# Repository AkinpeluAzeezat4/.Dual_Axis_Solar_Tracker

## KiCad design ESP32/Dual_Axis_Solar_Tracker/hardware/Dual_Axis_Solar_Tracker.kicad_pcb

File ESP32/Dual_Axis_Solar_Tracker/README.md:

# Dual Axis Solar Tracker

## Overview

This project is a Dual Axis Solar Tracking System built using the ESP32-WROOM-32UE microcontroller and an L298D motor driver module. The system automatically tracks the direction of sunlight using four LDR sensors and positions the solar panel for maximum light exposure using two DC motors.

The tracker also includes:

- Automatic night detection and sleep mode
- Rotary encoder based calibration and control
- Direction indication LEDs
- Manual movement mode
- Saved calibration settings using ESP32 Preferences (NVS)

The project is designed using a modular architecture for easier maintenance, debugging, scalability, and future upgrades.

---

# Features

- Dual axis solar tracking
- Automatic horizontal and vertical alignment
- Night detection using dedicated LDR
- Deep sleep power saving mode
- Rotary encoder controlled calibration
- Manual motor control mode
- Direction indication LEDs
- Saved calibration settings
- PWM motor speed control
- Modular PlatformIO structure

---

# Hardware Used

## Main Controller

- ESP32-WROOM-32UE

## Motor Driver

- L298D Dual H-Bridge Motor Driver

## Sensors

- 4 × LDRs for sun tracking
- 1 × LDR for night detection

## Inputs

- Rotary Encoder with push button

## Indicators

- 5 mm LEDs for direction indication

## Motors

- 2 × DC Gear Motors
  - Azimuth movement
  - Elevation movement

---

# Pin Configuration

## Motor Driver

| Signal | GPIO   |
| ------ | ------ |
| AZ_EN  | GPIO25 |
| AZ_IN1 | GPIO32 |
| AZ_IN2 | GPIO33 |
| EL_EN  | GPIO14 |
| EL_IN1 | GPIO26 |
| EL_IN2 | GPIO27 |

## LDR Sensors

| Sensor       | GPIO   |
| ------------ | ------ |
| Top Left     | GPIO4  |
| Top Right    | GPIO35 |
| Bottom Left  | GPIO39 |
| Bottom Right | GPIO34 |
| Night LDR    | GPIO36 |

## Rotary Encoder

| Signal | GPIO   |
| ------ | ------ |
| CLK    | GPIO18 |
| DT     | GPIO19 |
| SW     | GPIO23 |

## LEDs

| LED    | GPIO   |
| ------ | ------ |
| LEFT   | GPIO5  |
| RIGHT  | GPIO17 |
| UP     | GPIO16 |
| DOWN   | GPIO15 |
| STATUS | GPIO2  |

---

# LDR Wiring

3.3V ---- LDR ---- ADC PIN ---- 10k Resistor ---- GND

The ADC pin must be connected at the center point between the LDR and resistor.

---

# Project Structure

```text
lib/
├── Control/
├── Display/
├── Drivers/
├── Input/
├── Pins/
├── Sensors/
├── System/

src/
└── main.cpp
```

---

# Rotary Encoder Operation

## Short Press

Cycles through:

- AUTO_TRACK
- MANUAL_AZIMUTH
- MANUAL_ELEVATION
- CALIBRATE_DEADBAND
- CALIBRATE_NIGHT

## Long Press

Returns system to AUTO_TRACK mode.

## Rotation Functions

### MANUAL_AZIMUTH

Moves panel left and right.

### MANUAL_ELEVATION

Moves panel up and down.

### CALIBRATE_DEADBAND

Adjusts tracking sensitivity.

### CALIBRATE_NIGHT

Adjusts night detection threshold.

---

# Operating Guide

## Power On

1. Power the ESP32 and L298D driver.
2. Ensure all LDRs are exposed to light.
3. The status LED should begin breathing.
4. The system starts in AUTO_TRACK mode.

---

## Automatic Tracking

The system compares:

- Left vs Right light intensity
- Top vs Bottom light intensity

The motors automatically reposition the solar panel toward the strongest light source.

---

## Manual Control

Use short press to enter:

- MANUAL_AZIMUTH
- MANUAL_ELEVATION

Rotate the encoder to move the panel manually.

---

## Calibration

### Deadband Calibration

Higher deadband:

- Less motor movement
- Less jitter

Lower deadband:

- Faster response
- Higher sensitivity

### Night Threshold Calibration

Adjusts the darkness level required before entering sleep mode.

---

# Sleep Mode

When darkness is detected:

- Motors stop
- LEDs turn off
- ESP32 enters deep sleep

Wake sources:

- Rotary encoder button
- Timer wakeup

---

# PWM Motor Control

PWM is used on:

- GPIO25
- GPIO14

This provides:

- Smooth movement
- Adjustable speed
- Reduced motor stress

---

# Important Notes

- Use a separate motor power supply.
- Do not power motors directly from the ESP32.
- All grounds must be connected together.
- Use voltage dividers for all LDRs.
- GPIO34–39 are input-only pins.
- GPIO4 is ADC2 and may conflict with WiFi usage.

---

# PlatformIO Environment

```ini
[env:esp32dev]
platform = espressif32
board = esp32dev
framework = arduino
monitor_speed = 115200
```

---

# Uploading

## Build

```bash
pio run
```

## Upload

```bash
pio run --target upload
```

## Serial Monitor

```bash
pio device monitor
```

---

# Security Note

Sensitive information such as:

- WiFi password
- Access point password
- API keys

have intentionally been hidden using:

---

before publishing to GitHub.

---

# Future Improvements

- Astronomical tracking
- OTA updates
- Web dashboard
- Battery monitoring
- MPPT integration
- Weather integration
- Limit switches

---

# Author

Egbe Raymond

Electrical / Electronic Engineer
Embedded Systems Developer
Full Stack Developer

---

# License

This project is open-source and intended for educational and development purposes.

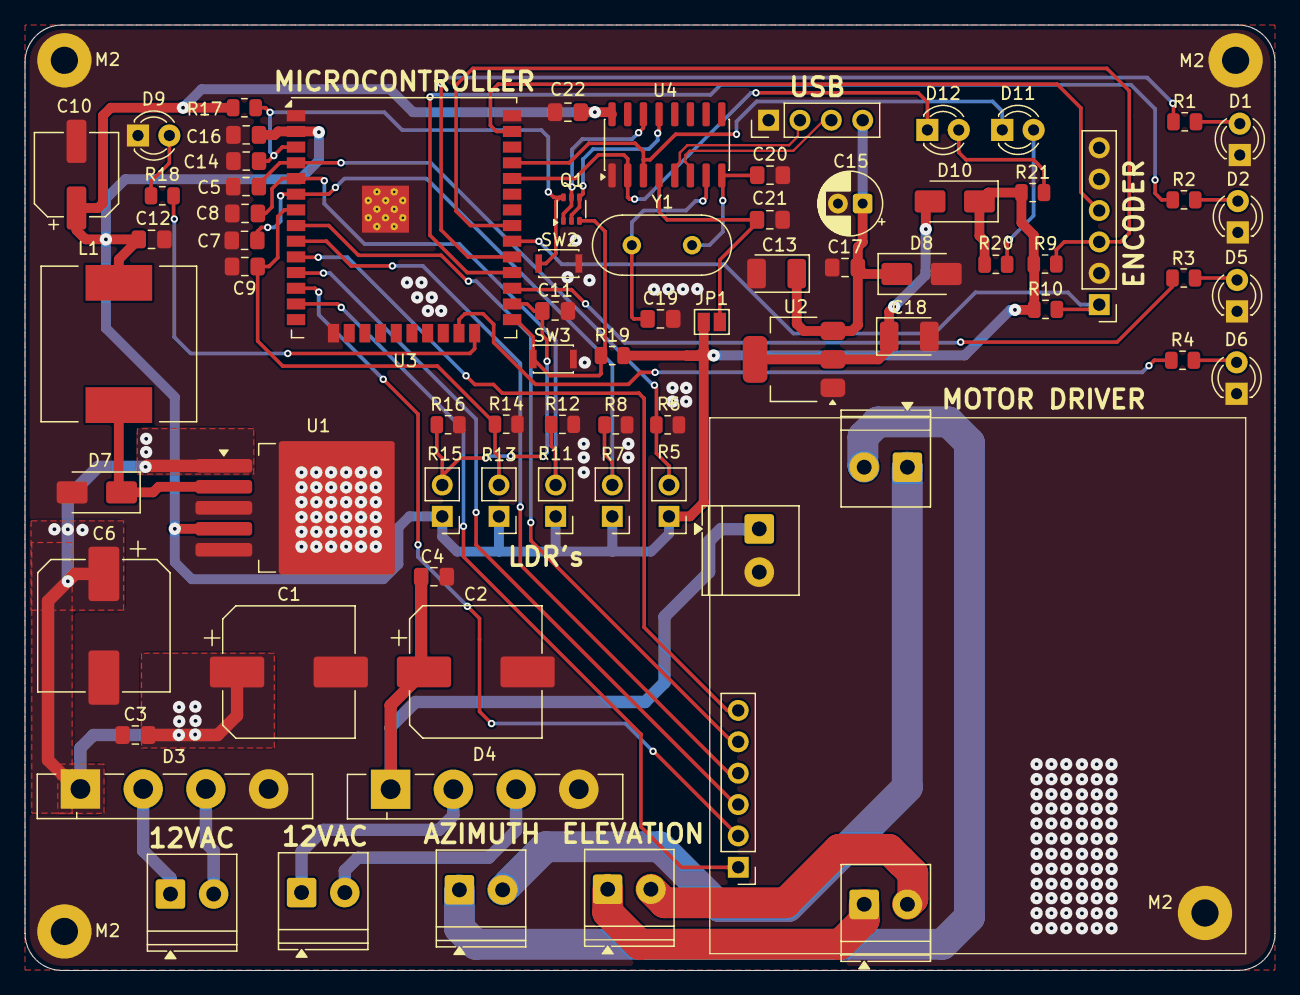
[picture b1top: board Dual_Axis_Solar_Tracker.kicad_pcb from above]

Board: 2 copper layers, 101.2 x 76.6 mm, 80 parts (1 on the bottom side), 52 nets.

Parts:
 : LOGO; CULogo
C1, C2: 470uF/25V; CP_Elec_10x12.5
C3, C4, C5, C7, C8, C9, C11, C12, C16, C17, C21, C22: 100nF; C_0805_2012Metric_Pad1.18x1.45mm_HandSolder
C6: 680uF_35V; CP_Elec_10x12.5
C10: 220uF_16V; CP_Elec_6.3x7.7
C13, C18: 4.7uF/16V; CP_EIA-3528-21_Kemet-B_HandSolder
C14: 470nF; C_0805_2012Metric_Pad1.18x1.45mm_HandSolder
C15: 10uF_16V; CP_Radial_D5.0mm_P2.00mm
C19, C20: 22pF; C_0805_2012Metric_Pad1.18x1.45mm_HandSolder
D1, D2, D5, D6, D9, D11: Red; LED_D3.0mm
D3, D4: GBU8M; Diode_Bridge_Vishay_GBU
D7: 1N5824; D_SMA
D8, D10: 1N5819; D_SMA
D12: Green; LED_D3.0mm
J1, J2: 12VAC; TerminalBlock_Phoenix_PT-1,5-2-3.5-H_1x02_P3.50mm_Horizontal
J3, J5: MOTOR; TerminalBlock_Phoenix_PT-1,5-2-3.5-H_1x02_P3.50mm_Horizontal
J4: SIGNAL; PinHeader_1x06_P2.54mm_Vertical
J6: 12V_IN; TerminalBlock_Phoenix_PT-1,5-2-3.5-H_1x02_P3.50mm_Horizontal
J7: USB_C Conn; PinHeader_1x04_P2.54mm_Vertical
JP1: SolderJumper-2_P1.3mm_Open_Pad1.0x1.5mm
L1: 33uH; L_12x12mm_H6mm
M1, M2: Geared Motor; TerminalBlock_Phoenix_PT-1,5-2-3.5-H_1x02_P3.50mm_Horizontal
M2#2, M2#3, M2#4, M2#5: MountingHole_2.2mm_M2_Pad
Q1: UMH3N; SOT-363_SC-70-6
R1, R2, R3, R4, R18, R20, R21: 330R; R_0805_2012Metric
R5, R7, R11, R13, R15: LDR; PinHeader_1x02_P2.54mm_Vertical
R6, R8, R9, R10, R12, R14, R16, R17, R19: 10k; R_0805_2012Metric
SW1: RotaryEncoder; PinHeader_1x06_P2.54mm_Vertical
SW2: RESET; SW_SPST_CK_KXT3
SW3: FLASH; SW_SPST_CK_KXT3
U1: LM2596S-3.3V; TO-263-5_TabPin6
U2: AMS1117-3.3; SOT-223-3_TabPin2
U3: ESP32-WROOM; ESP32-WROOM-32U
U4: CH340C; SOIC-16_3.9x9.9mm_P1.27mm
Y1: 12MHz; Crystal_HC49-4H_Vertical

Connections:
+3.3V: C10.1, C12.2, C16.2, C22.1, D10.1 (K), JP1.2 (B), L1.2, R5.1, R7.1, R9.2, R10.1, R11.1, R13.1, R15.1, R17.2, R19.2, R20.1, R21.1, U1.4 (FB), U3.2 (VDD), U4.16 (VCC)
+12V: C2.1, C4.2, D4.1 (+), J6.1
/+: J7.2, U4.5 (UD+)
/-: J7.3, U4.6 (UD-)
/DTR: Q1.2 (B1), Q1.4 (E2), U4.13 (~DTR)
/EN: C14.2, Q1.6 (C1), R17.1, SW2.2, U3.3 (EN)
/GPIO0: Q1.3 (C2), R19.1, SW3.2, U3.25 (IOA0)
/GPIO1/TX: D11.1 (K), U3.35 (TXD0/IO1), U4.3 (RXD)
/GPIO2: R18.1, U3.24 (IOA2)
/GPIO3/RX: D12.1 (K), U3.34 (RXD0/IO3), U4.2 (TXD)
/GPIO4: C11.1, R15.2, R16.1, U3.26 (IOA4)
/GPIO5: R1.1, U3.29 (IO5)
/GPIO14: J4.1, U3.13 (IOA14)
/GPIO15: R4.1, U3.23 (IOA15)
/GPIO16: R3.1, U3.27 (IO16)
/GPIO17: R2.1, U3.28 (IO17)
/GPIO18: R10.2, SW1.1 (A), U3.30 (IO18)
/GPIO19: R9.1, SW1.3 (B), U3.31 (IO19)
/GPIO23: SW1.4 (S1), U3.37 (IO23)
/GPIO25: J4.6, U3.10 (IOA25)
/GPIO26: J4.3, U3.11 (IOA26)
/GPIO27: J4.2, U3.12 (IOA27)
/GPIO32: J4.5, U3.8 (IOA32)
/GPIO33: J4.4, U3.9 (IOA33)
/GPIO34: C7.1, R7.2, R8.1, U3.6 (IA34)
/GPIO35: C9.1, R13.2, R14.1, U3.7 (IA35)
/GPIO36: C5.1, R5.2, R6.1, U3.4 (IA36)
/GPIO39: C8.1, R11.2, R12.1, U3.5 (IA39)
/RTS: Q1.1 (E1), Q1.5 (B2), U4.14 (~RTS)
GND: C1.2, C2.2, C3.1, C4.1, C5.2, C6.2, C7.2, C8.2, C9.2, C10.2, C11.2, C12.1, C13.2, C14.1, C15.2, C16.1, C17.1, C18.2, C19.2, C20.2, C21.1, C22.2, D1.1 (K), D2.1 (K), D3.4 (-), D4.4 (-), D5.1 (K), D6.1 (K), D7.2 (A), D8.2 (A), D9.1 (K), J6.2, J7.1, M2#2.1, M2#3.1, M2#4.1, M2#5.1, R6.2, R8.2, R12.2, R14.2, R16.2, SW1.2 (C), SW1.5 (S2), SW1.6 (MP), SW2.1, SW3.1, U1.3 (GND), U1.5 (~ON/OFF), U1.6 (GND), U2.1 (GND), U3.1 (GND), U3.15 (GND), U3.38 (GND), U3.39 (GND), U4.1 (GND)
unnamed: D1.2 (A), R1.2
unnamed: D2.2 (A), R2.2
unnamed: D5.2 (A), R3.2
unnamed: D6.2 (A), R4.2
unnamed: D7.1 (K), L1.1, U1.2 (OUT)
unnamed: C13.1, C15.1, C17.2, D8.1 (K), J7.4, U2.3 (VI)
unnamed: D9.2 (A), R18.2
unnamed: C18.1, D10.2 (A), U2.2 (VO)
unnamed: D11.2 (A), R20.2
unnamed: D12.2 (A), R21.2
unnamed: D3.2, J1.1
unnamed: D3.3, J1.2
unnamed: D4.2, J2.1
unnamed: D4.3, J2.2
unnamed: J3.1, M1.2 (-)
unnamed: J3.2, M1.1 (+)
unnamed: J5.1, M2.1 (+)
unnamed: J5.2, M2.2 (-)
unnamed: C21.2, JP1.1 (A), U4.4 (V3)
unnamed: C19.1, U4.7 (Xi), Y1.2
unnamed: C20.1, U4.8 (Xo), Y1.1
VCC: C1.1, C3.2, C6.1, D3.1 (+), U1.1 (VIN)

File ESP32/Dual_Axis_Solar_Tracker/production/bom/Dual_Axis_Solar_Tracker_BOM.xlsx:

Component | Designator | Value | Footprint | Quantity | Unit Price | Total Price
Capacitor | C1, C2 | 470uF/25V | 0805 | 2 | 200 | 400
 | C10 | 220uF/16V | 0805 | 1 | 200 | 200
 | C11, C12, C16, C17, C21, C22, C3, C4, C5, C7, C8, C9 | 100nF | 0805 | 12 | 100 | 1200
 | C13, C18 | 4.7uF/16V | 3528-21 | 2 | 200 | 400
 | C14 | 470nF | 0805 | 1 | 100 | 100
 | C15 | 10uF/16V | Radial D5.0mm_P2.00mm | 1 | 250 | 250
 | C19, C20 | 22pF | 0805 | 2 | 200 | 400
 | C6 | 680uF/35V | CP_Elec_10x12.5 | 1 | 200 | 200
Diode | D1, D11, D2, D5, D6, D9 | Red | LED_D3.0mm | 6 | 50 | 300
 | D10, D8 | 1N5819 | D_SMA | 2 | 200 | 400
 | D12 | Green | LED_D3.0mm | 1 | 50 | 50
 | D3, D4 | GBU8M | Diode_Bridge | 2 | 400 | 800
 | D7 | 1N5824 | D_SMA | 1 | 200 | 200
Motor | M1, M2 | Geared |  | 2 | 15000 | 30000
Dual Axis Complete mechanism |  |  |  | 1 | 60000 | 60000
Terminal Block | J1, J2, J3, J5,J6 | TerminalBlock_Phoenix | 1x02_P3.50mm | 4 | 400 | 1600
Pin Header | J4 | Vertical | 1x06_P2.54mm | 1 | 100 | 100
 | J7 | Vertical | 1x04_P2.54mm | 1 | 100 | 100
Inductor | L1 | 33uH | 12x12mm_H6mm | 1 | 400 | 400
Dual NPN digital transistor | Q1 | UMH3N | SOT-363 SC-70 | 1 | 400 | 400
Resistor | R1, R18, R2, R20, R21, R3, R4 | 330R | 0805 | 7 | 150 | 1050
 | R10, R12, R14, R16, R17, R19, R6, R8, R9 | 10K | 0805 | 9 | 150 | 1350
 | R11, R13, R15, R5, R7 | LDR | 1x02_P2.54mm | 5 | 400 | 2000
Rotary Encoder | SW1 | RotaryEncoder | nil | 1 | 1500 | 1500
Tact Button | SW2,SW3 | SPST_CK_KXT3 | nil | 2 | 300 | 600
Voltage Regulator | U1 | LM2596S-3.3V | TO-263-5 | 1 | 900 | 900
 | U2 | AMS1117-3.3 | SOT-223-3 | 1 | 400 | 400
Microcontroller | U3 | ESP32-WROOM | ESP32-WROOM-32U | 1 | 11000 | 11000
USB to Serial IC | U4 | CH340C | SOIC-16_3.9x9.9mm_P1.27mm | 1 | 600 | 600
Solar Panel |  | 12V/30W |  | 1 | 30000 | 30000
L298D motor Driver |  |  |  | 1 | 4000 | 4000
Transformer |  | 12V/1000mA |  | 2 | 3500 | 7000
Crystal Oscillator | Y1 | 12MHz | HC49-4H_Vertical | 1 | 300 | 300
PCB fabrication |  |  |  |  |  | 12000
Solar Pnael |  |  |  |  |  | 30000
Casing |  |  |  |  |  | 5000
Miscellaneous |  |  |  |  |  | 12000
Transportation fee |  |  |  |  |  | 7500
Total |  |  |  |  |  | 224700

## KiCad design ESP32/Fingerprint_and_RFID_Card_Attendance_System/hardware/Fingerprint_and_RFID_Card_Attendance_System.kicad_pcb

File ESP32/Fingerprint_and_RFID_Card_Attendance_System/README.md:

# Fingerprint and RFID Card Attendance System

## Overview

This project is a prototype Fingerprint and RFID Card Attendance System built around the ESP32-S3 DevKitC-1 module. The system is designed for schools, offices, workspaces, laboratories, and small organizations that need a simple local attendance device without depending on an online cloud server.

The main idea of this project is two-way attendance verification. A user must first tap a registered RFID card and then verify with the matching registered fingerprint before attendance is saved. This means the card alone cannot take attendance, and the fingerprint alone cannot take attendance. Both must belong to the same registered user.

The ESP32-S3 hosts a simple local web page, while the SD card inside the device acts as the backend storage for user records, attendance logs, and configuration settings.

The project is designed using a modular PlatformIO structure so that each part of the system can be tested, maintained, and upgraded independently.

---

# Features

- ESP32-S3 based attendance system
- RFID card and fingerprint AND verification
- AS608 fingerprint sensor support
- RC522 RFID card reader support
- SSD1309 128×64 OLED display using U8g2
- DS3231 RTC for date and time logging
- SD card backend storage
- Local web server hosted by the ESP32-S3
- Add/register user from the web page
- Remove/delete user from the web page
- Delete user removes the RFID link and fingerprint template
- Attendance IN and OUT mode
- Configurable for school or workspace use
- Download users, attendance, and config files from the web page
- Clear attendance log from the web page
- Simple OLED interface with minimal display lines
- Prototype keyboard/serial command support
- Modular PlatformIO code structure

---

# System Concept

The system works as a local attendance terminal. A user is registered with three main details:

- User ID
- RFID card UID
- Fingerprint template ID

During attendance, the user taps the RFID card first. The system checks the card against the records stored on the SD card. If the card is registered, the system asks for the fingerprint. The fingerprint sensor then searches for the fingerprint template. Attendance is saved only when the fingerprint ID matches the same user linked to the RFID card.

This gives the system stronger identity verification than using only card or fingerprint alone.

---

# Authentication Flow

```text
Tap RFID Card
      ↓
Check RFID UID in users.csv
      ↓
If card is registered, ask for fingerprint
      ↓
Scan fingerprint using AS608 sensor
      ↓
Compare fingerprint ID with the same user record
      ↓
If both match, save attendance to SD card
```

Attendance is not saved if:

- The RFID card is unknown
- The fingerprint is unknown
- The fingerprint belongs to another user
- The SD card is not ready
- The authentication timeout expires

---

# Web Page Functions

The ESP32-S3 creates a local Wi-Fi access point and hosts a simple web page. The web page reads from and writes to the SD card.

## Home Page

The home page shows:

- System name
- Workspace or school name
- Device IP address
- Current attendance mode
- Number of registered users
- Number of attendance records
- SD card status
- Last system event

It also includes quick forms for:

- Setting attendance mode
- Adding/registering a user
- Removing/deleting a user
- Downloading CSV files

## Users Page

The users page displays the content of `users.csv`. It also allows:

- Adding a user
- Removing a user

When a user is removed, the system removes the user from the SD card, unlinks the RFID card, and deletes the fingerprint template from the AS608 sensor.

## Attendance Page

The attendance page displays the content of `attendance.csv`. It also allows the attendance log to be cleared.

Clearing attendance does not delete registered users.

## Config Page

The config page allows the device to be configured for either school or workspace use.

Configurable fields include:

- System name
- Workspace or school name
- System type
- Default attendance mode
- Access Point SSID
- Access Point password

If the AP SSID or password is changed, the device should be restarted after saving.

---

# SD Card Backend

The SD card serves as the local backend storage device for the project.

The main files on the SD card are:

```text
/config.txt
/users.csv
/attendance.csv
```

## config.txt

Stores system configuration.

```text
system_name=Fingerprint RFID Attendance System
workspace_name=Prototype Workspace
workspace_type=school
ap_ssid=AttendanceSystem
ap_password=********
default_mode=IN
```

## users.csv

Stores registered user information.

```text
user_id,name,workspace,rfid_uid,fingerprint_id,active,created_at
```

Example:

```text
STU001,John Doe,Main,A1B2C3D4,1,1,2026-05-07 08:01:22
```

## attendance.csv

Stores attendance records.

```text
timestamp,user_id,name,method,direction,workspace,credential,record_hash
```

Example:

```text
2026-05-07 08:04:10,STU001,John Doe,RFID+FINGER,IN,Main,A1B2C3D4|FP:1,hash_value
```

---

# Hardware Used

## Main Controller

- ESP32-S3-DEVKITC-1-N8R8

## Identification Modules

- AS608 fingerprint sensor
- RC522 RFID card reader

## Storage and Timekeeping

- MicroSD card module
- DS3231 RTC module

## Display and User Interface

- SSD1309 128×64 OLED display
- Push buttons
- Buzzer
- Optional prototype keyboard/serial command input

## Power Section

- 5 V input supply
- LM2596S 3.3 V regulator section
- Common 3.3 V and 5 V rails

---

# Pin Configuration

## I2C Bus

| Function | ESP32-S3 GPIO |
| -------- | ------------- |
| OLED SDA / RTC SDA | GPIO8 |
| OLED SCL / RTC SCL | GPIO9 |

## Shared SPI Bus

| Function | ESP32-S3 GPIO |
| -------- | ------------- |
| SPI MOSI | GPIO11 |
| SPI SCK  | GPIO12 |
| SPI MISO | GPIO13 |

## RFID and SD Card Chip Select

| Function | ESP32-S3 GPIO |
| -------- | ------------- |
| RC522 SS | GPIO10 |
| RC522 RST | GPIO4 |
| SD Card CS | GPIO15 |

## Fingerprint Sensor UART

| Function | ESP32-S3 GPIO |
| -------- | ------------- |
| ESP32 TX to fingerprint RX | GPIO17 |
| ESP32 RX from fingerprint TX | GPIO18 |

## Buttons

| Button | ESP32-S3 GPIO |
| ------ | ------------- |
| BTN1 | GPIO1 |
| BTN2 | GPIO6 |
| BTN3 | GPIO7 |
| BTN4 | GPIO16 |
| BTN5 | GPIO3 |

## Other Pins

| Function | ESP32-S3 GPIO |
| -------- | ------------- |
| Buzzer | GPIO5 |
| Battery ADC | GPIO2 |
| USB D- | GPIO19 |
| USB D+ | GPIO20 |

GPIO19 and GPIO20 are reserved for USB use on the ESP32-S3. In the current firmware, the status LED is disabled in the pin file to avoid interfering with future USB keyboard support.

---

# OLED Display

The OLED uses the SSD1309 128×64 U8g2 constructor:

```cpp
U8G2_SSD1309_128X64_NONAME0_F_HW_I2C u8g2(U8G2_R0, U8X8_PIN_NONE);
```

The display is intentionally kept minimal. It only shows short messages such as:

- System starting
- Tap card first
- Place finger now
- Attendance saved
- Authentication failed
- SD card error
- User registered
- User deleted

---

# Project Structure

```text
lib/
├── Actuators/
│   └── buzzer/
├── Communication/
│   ├── local_server/
│   └── WiFi/
├── Control/
│   └── attendance_manager/
├── Display/
│   ├── led_indicator/
│   └── oled_screen/
├── Input/
│   ├── buttons/
│   ├── fingerprint/
│   ├── keyboard_input/
│   └── RFID/
├── Pins/
├── Power/
│   └── battery_level/
├── Storage/
│   └── sd_card/
└── System/
    ├── error_handling/
    ├── reset/
    ├── rtc/
    └── sleep_wake/

src/
└── main.cpp
```

---

# Module Summary

## Pins

Contains all GPIO assignments from the schematic. This makes it easier to update pins later without editing every module.

## Attendance Manager

Handles the main logic of the project:

- User enrollment
- RFID and fingerprint linking
- AND verification
- Attendance logging
- Delete user coordination
- IN and OUT attendance mode

## Local Server

Hosts the web page and provides routes for:

- Home
- Users
- Attendance
- Config
- Add user
- Delete user
- Save config
- Download CSV files
- Clear attendance log
- Status API

## SD Card

Stores all backend files used by the web page and firmware.

## Fingerprint

Handles AS608 fingerprint enrollment, search, and template deletion.

## RFID

Handles RC522 card scanning and UID reading.

## OLED Screen

Shows short system status messages.

## RTC

Provides timestamp for attendance records.

## Wi-Fi Manager

Creates the ESP32-S3 access point for the local server.

## Keyboard Input

Provides prototype serial commands such as:

```text
IN
OUT
STATUS
ENROLL,STU001,John Doe,Main
DELETE,STU001
```

---

# Operating Guide

## 1. Power On

1. Insert the SD card.
2. Power the device.
3. Wait for the OLED to show that the system is ready.
4. The device creates a Wi-Fi access point.

Default AP details:

```text
SSID: AttendanceSystem
Password: ********
```

The default IP is usually:

```text
http://192.168.4.1
```

## 2. Connect to the Web Page

1. Connect a phone or laptop to the device Wi-Fi.
2. Open a browser.
3. Enter the device IP address.
4. The local attendance web page will open.

## 3. Add / Register User

1. Open the web page.
2. Enter the user ID, name, and workspace/class/department.
3. Click **Start Registration**.
4. Tap the RFID card on the reader.
5. Place the finger when the OLED asks.
6. The system saves the user to the SD card.

The user is now linked to both RFID card and fingerprint.

## 4. Take Attendance

1. Select IN or OUT mode.
2. Tap the registered RFID card.
3. Place the matching registered finger.
4. If both match the same user, attendance is saved.

## 5. Remove User

1. Open the Users page or Home page.
2. Enter the user ID.
3. Click **Delete User**.
4. The system removes the user record from the SD card.
5. The RFID card is automatically unlinked.
6. The fingerprint template is deleted from the AS608 sensor.

## 6. Download Records

Use the download links to export:

- Users CSV
- Attendance CSV
- Config file

## 7. Clear Attendance

The attendance log can be cleared from the Attendance page.

This only clears `attendance.csv`. It does not delete users.

---

# PlatformIO Environment

```ini
[env:esp32-s3-devkitc-1]
platform = espressif32@6.5.0
board = esp32-s3-devkitc-1
framework = arduino
monitor_speed = 115200
upload_speed = 921600
lib_ldf_mode = deep+

lib_deps =
    olikraus/U8g2@^2.35.30
    adafruit/Adafruit Fingerprint Sensor Library@^2.1.3
    miguelbalboa/MFRC522@^1.4.11
    adafruit/RTClib@^2.1.4
    adafruit/Adafruit BusIO@^1.16.1

build_flags =
    -DARDUINO_USB_MODE=1
    -DARDUINO_USB_CDC_ON_BOOT=1
```

---

# Uploading

## Build

```bash
pio run
```

## Upload

```bash
pio run --target upload
```

## Serial Monitor

```bash
pio device monitor
```

---

# Security and Privacy Notes

This is still a prototype, but the following privacy ideas are considered:

- The system does not store raw fingerprint images on the SD card.
- Fingerprint templates are stored inside the AS608 fingerprint sensor.
- The SD card stores user information and attendance records in CSV format.
- Attendance records include a SHA-256 hash for basic tamper checking.
- The local web page is hosted on the ESP32-S3 access point and is intended for local use.
- Sensitive information such as passwords should be hidden before publishing to GitHub.

For a production version, stronger security can be added, such as encrypted SD card records, login authentication for the web page, stronger access control, and automatic backup.

---

# Important Notes

- This project is a prototype.
- The SD card must be inserted before startup.
- The fingerprint sensor storage size depends on the exact AS608 module used.
- The current firmware limits fingerprint IDs to 1–200.
- The attendance method is strictly RFID plus fingerprint.
- Do not use GPIO19 and GPIO20 for normal LEDs if USB support is needed.
- Keep all grounds common between the ESP32-S3 and external modules.
- Use stable power because the SD card and fingerprint sensor can draw current during operation.

---

# Future Improvements

- Full USB HID keyboard support
- Admin login for the local web page
- Better user table display instead of raw CSV preview
- Encrypted SD card records
- Backup and restore function
- Export by date range
- OTA firmware update
- Real-time dashboard refresh
- Better attendance analytics
- Cloud sync option

---

# Author

Egbe Raymond

Electrical / Electronic Engineer  
Embedded Systems Developer  
Full Stack Developer

---

# License

This project is open-source and intended for educational, prototyping, and development purposes.

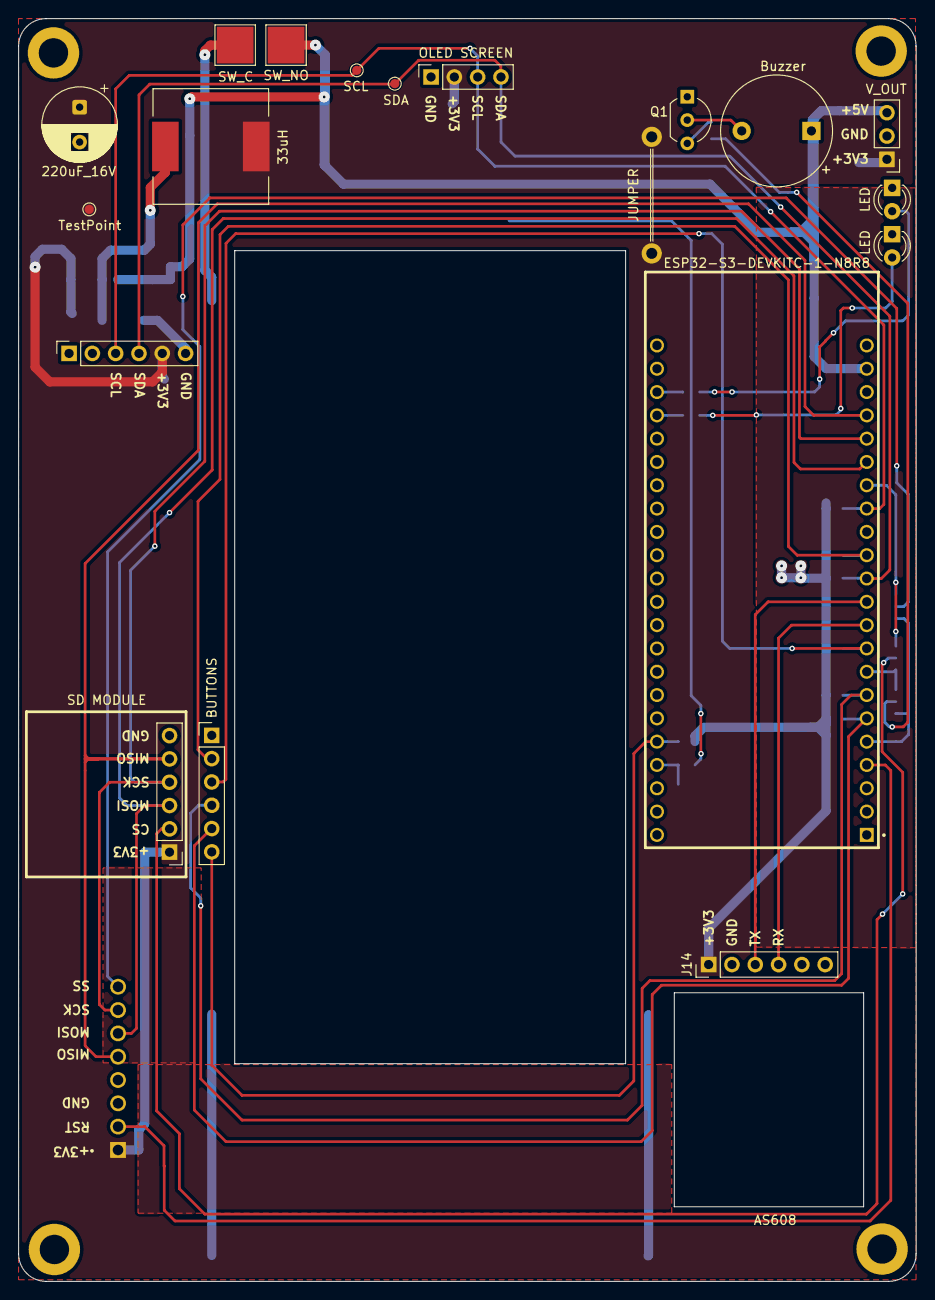
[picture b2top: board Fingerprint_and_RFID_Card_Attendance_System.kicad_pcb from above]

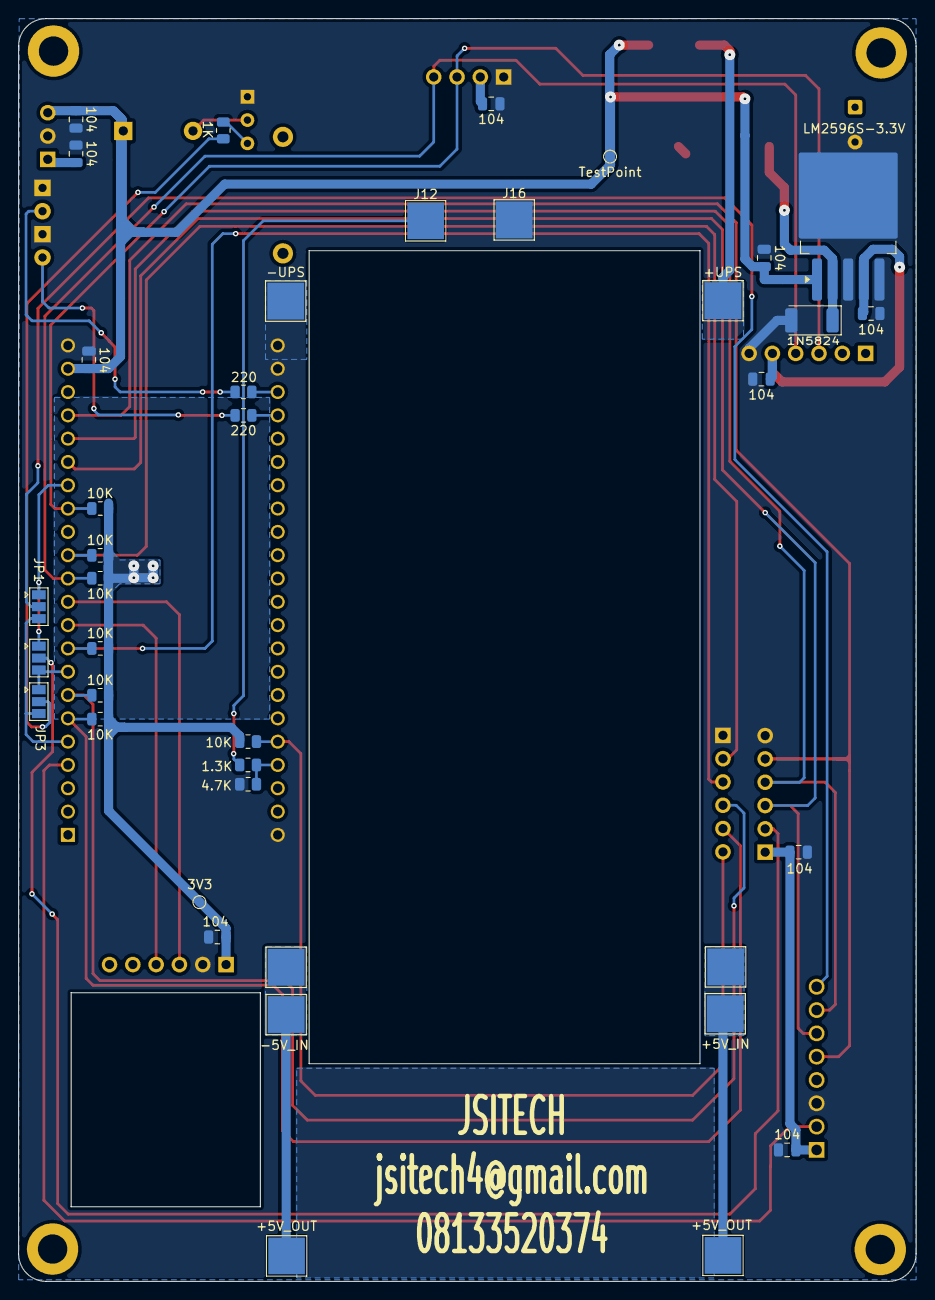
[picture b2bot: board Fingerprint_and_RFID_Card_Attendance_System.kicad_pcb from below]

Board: 2 copper layers, 97.8 x 137.6 mm, 58 parts (39 on the bottom side), 34 nets.

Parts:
3.3V2: 3V3; TestPoint_Pad_D1.0mm
3.3V5, 5V1: TestPoint; TestPoint_Pad_D1.0mm
BZ1: Buzzer; Buzzer_12x9.5RM7.6
C1, C2, C3, C4, C5, C7, C8, C9, C10, C11: 104; C_0805_2012Metric
C6: 220uF_16V; CP_Radial_D8.0mm_P3.80mm
D1, D3: LED; LED_D3.0mm
D2: 1N5824; D_2010_5025Metric
J1: RTC; PinSocket_1x06_P2.54mm_Vertical
J2: OLED SCREEN; PinSocket_1x04_P2.54mm_Vertical
J3, J4: +5V_OUT; TestPoint_Pad_4.0x4.0mm
J5, J5#2: +5V_IN; TestPoint_Pad_4.0x4.0mm
J6, J6#2: -5V_IN; TestPoint_Pad_4.0x4.0mm
J9: +UPS; TestPoint_Pad_4.0x4.0mm
J10: -UPS; TestPoint_Pad_4.0x4.0mm
J11: V_OUT; PinHeader_1x03_P2.54mm_Vertical
J12: +BATT; TestPoint_Pad_4.0x4.0mm
J13: BUTTONS; PinHeader_1x06_P2.54mm_Vertical
J14: AS608; PinHeader_1x06_P2.54mm_Vertical
J15: SD MODULE; PinHeader_1x06_P2.54mm_Vertical
J16: -BATT; TestPoint_Pad_4.0x4.0mm
J17: SW_C; TestPoint_Pad_4.0x4.0mm
J18: SW_NO; TestPoint_Pad_4.0x4.0mm
JP1, JP2, JP3: SolderJumper-3_P1.3mm_Open_Pad1.0x1.5mm
L1: 33uH; L_12x12mm_H4.5mm
Q1: 2SC1815; TO-92_Inline_Wide
R1, R2, R7, R8, R9, R10, R11: 10K; R_0805_2012Metric
R3, R4: 220; R_0805_2012Metric
R5: 1.3K; R_0805_2012Metric
R6: 4.7K; R_0805_2012Metric
R12: 1K; R_0805_2012Metric
SCL1: SCL; TestPoint_Pad_D1.0mm
SDA1: SDA; TestPoint_Pad_D1.0mm
U1: ESP32-S3-DEVKITC-1-N8R8; ESP32-S3-DEVKITC
U2: LM2596S-3.3V; TO-263-5_TabPin3
U3: RC522; RC522 RFID

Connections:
+3.3V: 3.3V2.1, 3.3V5.1, C1.1, C2.1, C5.1, C6.1, C8.1, C9.1, C10.1, C11.1, J1.5, J2.2, J11.1, J14.1, J15.1, L1.2, R1.1, R2.1, R7.1, R8.1, R9.1, R10.1, R11.1, U2.4 (FB), U3.1 (VCC)
+5V: 5V1.1, BZ1.1 (+), C3.1, C4.1, C7.1, J11.3, J18.1, U1.J1_21 (5V0), U2.1 (VIN)
/BTN1: J13.6, R11.2, U1.J3_5 (GPIO2)
/BTN2: J13.5, R10.2, U1.J1_6 (GPIO6)
/BTN3: J13.4, R9.2, U1.J1_7 (GPIO7)
/BTN4: J13.3, R8.2, U1.J1_9 (GPIO16)
/BTN5: J13.2, R7.2, U1.J1_13 (GPIO3)
/CS1: JP1.1 (A), JP2.1 (A), U1.J1_16 (GPIO10)
/CS2: JP2.3 (C), JP3.1 (A), U1.J1_8 (GPIO15)
/CS3: JP1.3 (C), JP3.3 (C), U1.J1_5 (GPIO5)
/RC522 RST: U1.J1_4 (GPIO4), U3.2 (RST)
/RC522 SS: JP1.2 (B), U3.8 (SS/SDA/RX)
/RX: J14.3, U1.J1_11 (GPIO18)
/SCL: J1.3, J2.3, R2.2, SCL1.1, U1.J1_15 (GPIO9)
/SD CARD CS: J15.2, JP2.2 (B)
/SDA: J1.4, J2.4, R1.2, SDA1.1, U1.J1_12 (GPIO8)
/SHARED_MISO: J15.5, U1.J1_19 (GPIO13), U3.5 (MISO/SCL/TX)
/SHARED_MOSI: J15.3, U1.J1_17 (GPIO11), U3.6 (MOSI)
/SHARED_SCK: J15.4, U1.J1_18 (GPIO12), U3.7 (SCK)
/TX: J14.4, U1.J1_10 (GPIO17)
GND: C1.2, C2.2, C3.2, C4.2, C5.2, C6.2, C7.2, C8.2, C9.2, C10.2, C11.2, D1.1 (K), D2.2 (A), D3.1 (K), J1.6, J2.1, J10.1, J11.2, J13.1, J14.2, J15.6, J16.1, Q1.1 (E), R6.2, U1.J1_22 (GND3), U1.J3_1 (GND), U1.J3_21 (GND1), U1.J3_22 (GND2), U2.3 (GND), U2.5 (~ON/OFF), U3.3 (GND)
unnamed: BZ1.2 (-), Q1.2 (C)
unnamed: D1.2 (A), R3.1
unnamed: D2.1 (K), L1.1, U2.2 (OUT)
unnamed: D3.2 (A), R4.1
unnamed: J3.1, J5.1, J5#2.1
unnamed: J4.1, J6.1, J6#2.1
unnamed: J12.1, R5.1
unnamed: J9.1, J17.1
unnamed: JP3.2 (B), R12.1
unnamed: Q1.3 (B), R12.2
unnamed: R5.2, R6.1, U1.J3_4 (GPIO1)
unnamed: R4.2, U1.J3_19 (USB_D+/GPIO20)
unnamed: R3.2, U1.J3_20 (USB_D-/GPIO19)
